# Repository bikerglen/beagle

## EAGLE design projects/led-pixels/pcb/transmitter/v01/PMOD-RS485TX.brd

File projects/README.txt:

-------------
led-panel-v01
-------------

Code to drive a single SparkFun / Adafruit 32x32 LED panel using
a BeagleBone Black and a ValentFX LogiBone FPGA board. 

Blog Post Here:

http://bikerglen.com/blog/driving-a-32x32-rgb-led-matrix-with-a-beaglebone-black-and-an-fpga/

Tutorial Here:

http://bikerglen.com/projects/lighting/led-panel-1up/

Video Demonstration Here:

http://youtu.be/OIyI8KaPdwk

-------------
led-panel-6up
-------------

Code to drive up to six SparkFun / Adafruit 32x32 LED panels using
a BeagleBone Black and a ValentFX LogiBone FPGA board. 

Blog Post Here:

http://bikerglen.com/blog/expanding-the-beaglebone-black-and-fpga-to-drive-6-or-more-panels/

Video Demonstration Here:

http://www.youtube.com/watch?v=LBeVMGOgWvY

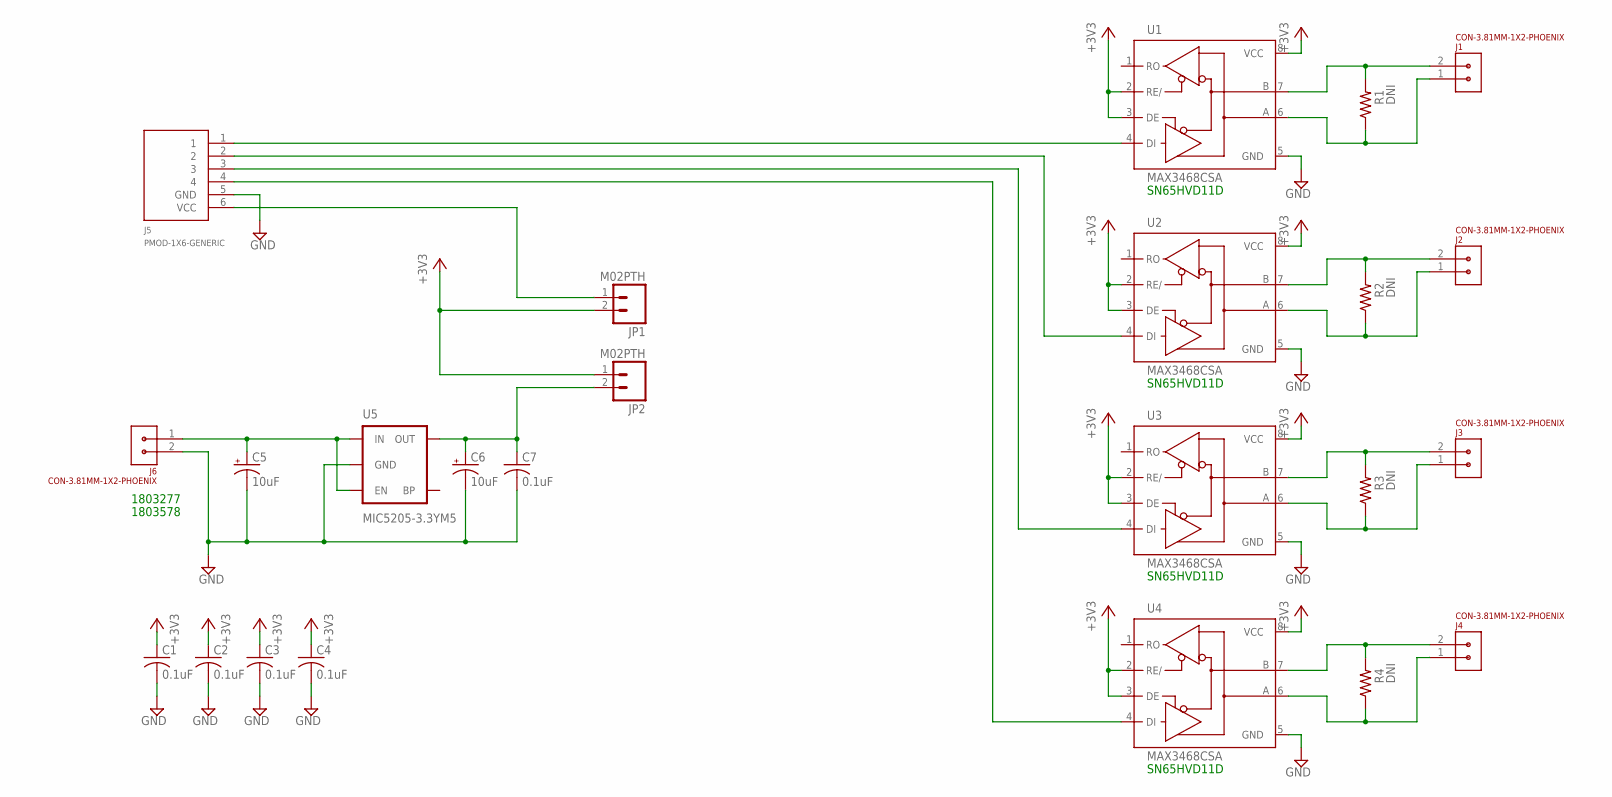
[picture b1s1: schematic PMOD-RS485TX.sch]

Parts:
C1, C2, C3, C4, C7: 0.1uF; C1206
C5, C6: 10uF; PANASONIC_D
J1, J2, J3, J4, J6: CON-3.81MM-1X2-PHOENIX; CON-PHOENIX-3.81-1X2-RA
J5: PMOD-1X6-GENERIC; CON-PMOD-1X6
JP1, JP2: M02PTH; 1X02
R1, R2, R3, R4: DNI; M1206
U1, U2, U3, U4: MAX3468CSA; SO08
U5: MIC5205-3.3YM5; SOT23-5

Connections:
+3V3: C1.1, C2.1, C3.1, C4.1, JP1.2, JP2.1, U1.2 (RE/), U1.3 (DE), U1.8 (VCC), U2.2 (RE/), U2.3 (DE), U2.8 (VCC), U3.2 (RE/), U3.3 (DE), U3.8 (VCC), U4.2 (RE/), U4.3 (DE), U4.8 (VCC)
+5V: C5.+, J6.1, U5.1 (IN), U5.3 (EN)
GND: C1.2, C2.2, C3.2, C4.2, C5.-, C6.-, C7.2, J5.5 (GND), J6.2, U1.5 (GND), U2.5 (GND), U3.5 (GND), U4.5 (GND), U5.2 (GND)
unnamed: C6.+, C7.1, JP2.2, U5.5 (OUT)
unnamed: J2.2, R2.2, U2.7 (B)
unnamed: J2.1, R2.1, U2.6 (A)
unnamed: J3.2, R3.2, U3.7 (B)
unnamed: J1.2, R1.2, U1.7 (B)
unnamed: J3.1, R3.1, U3.6 (A)
unnamed: J1.1, R1.1, U1.6 (A)
unnamed: J4.2, R4.2, U4.7 (B)
unnamed: J4.1, R4.1, U4.6 (A)
unnamed: J5.1, U1.4 (DI)
unnamed: J5.2, U2.4 (DI)
unnamed: J5.3, U3.4 (DI)
unnamed: J5.4, U4.4 (DI)
unnamed: J5.6 (VCC), JP1.1

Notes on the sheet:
SN65HVD11D
1803277
1803578

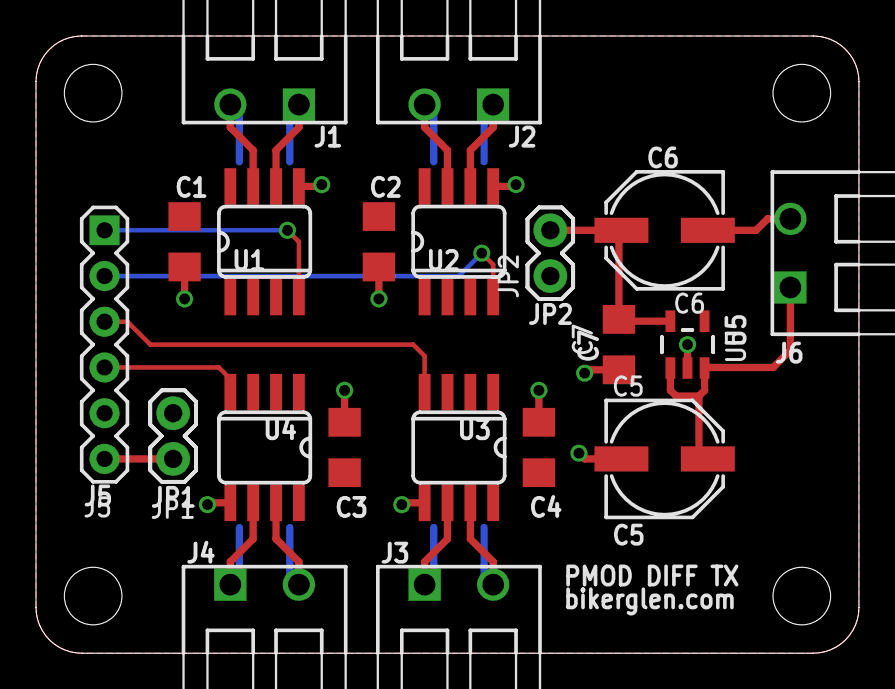
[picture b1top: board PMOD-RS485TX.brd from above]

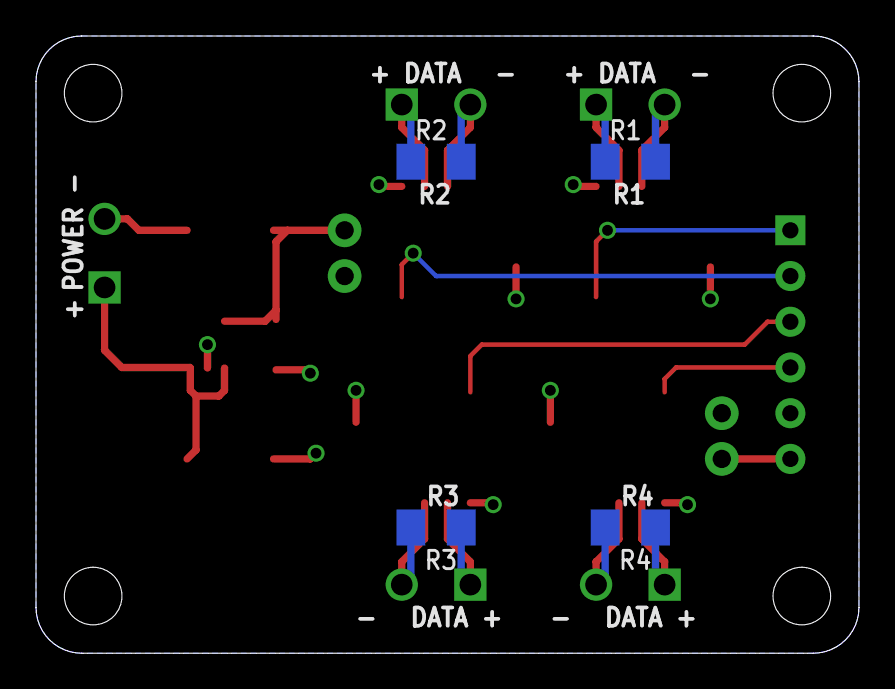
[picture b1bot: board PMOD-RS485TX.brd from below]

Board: 2 copper layers, 45.7 x 34.3 mm, 24 parts (4 on the bottom side), 17 nets.

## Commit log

2014-02-13 Initial checkin.
2014-02-13 changed type for circle object to eliminate warning
2014-02-14 added simplified constructor with reasonable defaults
2014-02-14 fixed tabs and spaces
2014-02-14 fixed tabs and spaces, created new simple constructors
2014-02-14 expanded all tabs
2014-02-14 added comments, improved code to ensure bounds of PERM table are not exceeded.
2014-02-14 better comment about reason to combine noises
2014-02-14 Added Casey's copyright notice for noise function.
2014-02-14 example raw file for use with picture.cpp
2014-02-14 expanded tabs
2014-02-15 Initial checkin of LED panel driver RTL.
2014-02-15 added getters and setters; made noise method private
2014-02-15 add color wash code
2014-02-15 made usable with different panel heights and widths
2014-02-15 fixed cut and paste error
2014-02-15 added twinkle, runtwinkle
2014-02-15 added more files to clean list
2014-02-15 added missing targets
2014-02-16 new targets
2014-02-16 solid color wipe LtoR, RtoL, TtoB, BtoT
2014-02-16 changed when pattern complete is asserted, run direction changing
2014-02-23 another static image
2014-02-23 removed last remaining systemverilog constructs
2014-02-28 initial checkin
2014-02-28 rebuilt with minimal set of project files
2014-03-08 forced some outputs to IOBs, added commands to analyze skew between sclk and data signals
2014-03-18 fixed comment to reflect code / reality
2014-03-30 wall hanging bracket for rear of 6up led panel frame
2014-03-30 frame for holding 6 x 32x32 6mm pitch RGB LED panels.
2014-03-30 front panel express design file with dimensions of a single 32x32 6mm pitch RGB LED panel.
2014-03-30 RTL for driving 6 LED panels at once, include global dimming, tightened SCLK/RGB data timing.
2014-04-01 updated ucf for revision ra3 of logibone hardware
2014-04-01 updated bit file for revision ra3 logibone hardware
2014-04-02 added build environment for 6up FPGA
2014-04-03 added code to run fixed point Perlin noise
2014-04-04 changed scaling factor
2014-04-04 description of projects in this directory
2014-04-04 added links to write up / tutorial and youtube video
2014-04-10 3D printed brackets to make an LED panel cube
2014-04-12 added links to blog posts
2014-04-17 added beta (RA2) and production (RA3) bitfiles for 6up project
2014-04-17 added SKP and STL for stainless steel cube hanging bracket
2014-04-17 renamed file to add r01 suffix
2014-04-17 added STL for cube corner hanging bracket
2014-05-01 device tree setup files for use with ra2 beta ubuntu image
2014-05-01 added files and instructions for ra2 and r01 versions of the hardware and ubuntu images
2014-05-01 Moved files into ra2 directory to separate them from r01 files
2014-05-01 deleted files that were moved to ra2 directory
2014-05-01 Moved mechanical files for flat panel and 3d cube into their own directories
2014-05-16 fixed RGB ordering
2014-06-01 Added 3D printed enclosure tutorial files.
2014-06-01 adding sketchup and stl files for enclosure as built in April/May 2014
2014-06-01 initial revision of RS422/485 differential transmitter board
2014-09-08 Changed addresses for Kernel Update
    Logi-Kernel was changed to use 16 bit addressing instead of byte
    addressing. Created new folder for chages. Created new folder and
    copied old files to maintain legacy code.
    address register now 0x0008
    data register now 0x0009
    buffer select register now 0x000A
2014-09-08 Added BB-BONE-LOGIBONE to disable
    Changes eEnv.text_Edits.txt to disable BB-BONE-LOGIBONE because new
    Logi-Bones have eeprom programmed and will automatically load default
    overlay
2014-09-08 unexport default device tree overlay
    If logi bone has eeprom, the kernal will load the device tree overlay on
    boot. Added code to unexport default tree overlay.
2015-09-18 Modified software makefile to be less repetitive. Modified software to utilize a single WriteLines method
2015-09-18 Modified FPGA code to access pixels in an adress one-to-one fashion. Also modified the buffer selection to happen automatically
2015-09-18 Modified setup on newer valentfx ubuntu image
2015-09-18 added missing globals.cpp
2015-09-18 removed non used binaries from Makefile
2015-09-18 tweaks to work with latest valentfx ubuntu build
2015-09-19 updated bitfile for Verilog changes

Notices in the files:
parts and their libraries:
SparkFun-PowerIC: Licensing: Creative Commons ShareAlike 4.0 International - https://creativecommons.org/licenses/by-sa/4.0
